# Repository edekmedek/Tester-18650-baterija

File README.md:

# Tester18650 R26 — dovršeno trasiranje i DRC

Izvorni R25 projekt u `Downloads` nije mijenjan. R26 je zasebna radna kopija.

## Napravljene promjene

- D1 i R5 premješteni su s koordinata izvan ploče na pločicu.
- R1, R2, R3 i R4 preraspoređeni su tako da nema fizičkih preklapanja s NodeMCU, INA219 i držačem baterije.
- Sve definirane mreže trasirane su na F.Cu i B.Cu.
- Vodovi snage (`BAT_PLUS`, `BAT_MINUS_GND`, `LOAD_PLUS`, `LOAD_RETURN`) izvedeni su širinom 1,0 mm.
- Upravljački i mjerni vodovi izvedeni su širinama 0,5–0,6 mm.
- Rub silkscreena INA219 footprinta povučen je unutar obrisa ploče.
- Sakriveni su natpisi koji su prelazili preko padova ili ruba ploče.

## Završni DRC

- DRC violations: 7 upozorenja, 0 grešaka
- Unconnected pads: 0
- Footprint errors: 0
- Nema kratkih spojeva, clearance grešaka, presijecanja vodova ni courtyard preklapanja.

Svih 7 preostalih upozorenja su `lib_footprint_mismatch`: lokalno prilagođeni footprintovi u PCB-u razlikuju se od primjeraka u projektnoj biblioteci. Nisu automatski zamijenjeni jer bi osvježavanje iz biblioteke moglo vratiti ranija, nepotvrđena mapiranja pinova.

## Obavezna provjera prije izrade

- Potvrditi fizičku orijentaciju zaštitne diode D1.
- Potvrditi INA219 IN+/IN− orijentaciju na stvarnom modulu.
- Iako je Q1 mapiranje ranije označeno kao korisnički potvrđeno, preporučuje se završna usporedba s točnom izvedbom C3209 prije narudžbe PCB-a.
- Provjeriti termički razmak i očekivanu disipaciju oba otpornika 22 Ω / 5 W u stvarnom kućištu.

Datoteka `DRC_R26.txt` sadrži puni završni izvještaj.

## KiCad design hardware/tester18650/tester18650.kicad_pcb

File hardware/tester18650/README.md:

# Tester 18650 — KiCad 10, shema R2 i PCB P3

**Funkcionalni strujni krug je spojen u uređivoj shemi. Fizičko ožičenje i C3209 pinout nisu potvrđeni. ERC nije čist: 11 pogrešaka i 1 upozorenje.**

R2 nastavlja postojeći projekt iz commita `bfc8b56`: isti `.kicad_pro`, isti list i isti UUID-i jedanaest zadržanih simbola. Nije izrađen zaseban projekt. Prekidi TP1–TP4 uklonjeni su i zamijenjeni stvarnim električnim vodovima. Raspored lista i oznake priključaka uređeni su radi čitljivosti.

## PCB prema fotografijama

Dodan je [uređivi PCB P3](tester18650.kicad_pcb), [PDF komponenti](tester18650_pcb_components.pdf), [PDF prednjeg bakra](tester18650_pcb_layout.pdf) i [3D prikaz](tester18650_pcb_3d.png). Raspored koristi korisnikove fotografije kao glavni vizualni izvor. Detalji, izvori footprintova i ograničenja su u [PCB.md](PCB.md). P3 ima osam mapiranih K1 padova te rutirane COM/BAT+ i NO/opterećenje; ukupno 33 segmenta na sedam bakrenih mreža. Q1 pinout ostaje nepotvrđen. Referentni/zamjenski 3D modeli jasno su označeni. **DRC: 2 nepovezane veze + 5 upozorenja usporedbe sa shemom; nije za proizvodnju.**

## Funkcionalni krug u shemi

```text
BAT+ → K1 COM (11) → NO (14) → (R1 22 Ω / 5 W || R2 22 Ω / 5 W)
     → VIN+ → RSH1, interni shunt INA219 → VIN− → BAT−
```

COM–NO koristi se prema korisnikovu zadatku i ponašanju firmwarea: aktivacija releja uključuje opterećenje. NC (12) ne sudjeluje u pražnjenju; ostavljen je otvoren i njegov je ERC nalaz vidljiv. Pet funkcija 11/12/14 i A1/A2 sada je mapirano na osam padova K1 prema korisnikovoj proizvođačkoj potvrdi i provjerljivoj KiCad 16A referenci. Izravna usporedba točnih TE dimenzija/tolerancija ostaje otvorena; mapiranje ne potvrđuje fizičko ožičenje korisnikova primjerka.

**VIN+ je spojen prema opterećenju, VIN− prema BAT− kao izričito označena projektna pretpostavka.** Firmware koristi `fabsf(ina219_current)`, pa pozitivna prikazana struja nije dokaz fizičkog polariteta. RSH1 prikazuje postojeći interni mjerni element modula, ne dodatni vanjski otpornik. Njegova je vrijednost označena `vrijednost ?`; firmware parametar `0.11425 Ω` naveden je zasebno kao kalibracijski podatak. RSH1 je izuzet iz zasebnog BOM-a i PCB-a jer pripada modulu.

Zavojnica K1 ostaje spojena između +5 V i kolektora Q1, oznake C3209. Nazivna zavojnica je 6 V DC, a dokumentirani pogon 5 V. Nije provjerena margina uklapanja. Q1 koristi generički NPN simbol; B/C/E su funkcije, a 1/2/3 nisu potvrđeni raspored nožica kućišta.

## Izvori za upravljanje i mjerenje

Pregledan je puni [ESPHome firmware](../../firmware/battery-tester-8266-wifi-test.yaml), njegov [opis](../../firmware/README.md), aktualna dokumentacija i korisnikove potvrde. Stare D6–D12 sheme nisu korištene kao dokaz.

Firmware potvrđuje `nodemcuv2`, GPIO14 bez inverzije (`ALWAYS_OFF` i isključenje pri bootu), SDA GPIO2, SCL GPIO5, I²C 100 kHz, INA219 `0x40` i A0 s faktorom `9.5079`. Prikazane su i radne napomene: uključivanje nakon 500 ms i početni cutoff 3,00 V kroz pet uzastopnih sekundi. Firmware nije izmijenjen ni flashan.

Firmware ne određuje bazni otpornik, spoj emitera, zaštitnu diodu, redoslijed otpornika djelitelja ni napajanja modula. Zato nema izmišljenog otpornika između GPIO14 i baze, izravnog kratkog spoja GPIO14–B, pretpostavljenog emitera na masi ni odabranog redoslijeda R3/R4. Pouzdani spojevi +5 V → zavojnica → kolektor i GPIO-i su nacrtani; preostale granice jasno su označene N3/N4. R3 = 10 kΩ i R4 = 20 kΩ zadržani su s otvorenim krajevima jer faktor A0 ne određuje njihovu fizičku topologiju.

## Logička sučelja i oznake

J1/J2 koriste standardni `Connector_Generic:Conn_01x06` kao logičke prikaze modula. Od faze P1 povezani su s referentnim PCB footprintovima i uključeni u pločicu/BOM; to nije potvrda mehaničkog pristajanja konkretnih modula. **Brojevi 1–6 su indeksi sheme, ne fizički raspored nožica.** Svaki priključak dodatno je označen funkcijom na listu. TP5 i TP6 su samo dokumentacijski završeci prema nepoznatom baznom sklopu i djelitelju; nisu ugrađene testne točke.

| Indeks | J1 — NodeMCU ESP8266 | J2 — INA219 modul |
|---|---|---|
| 1 | D5 / GPIO14 → TP5, bazni sklop nepoznat | SDA ↔ GPIO2 |
| 2 | D4 / GPIO2 ↔ SDA | SCL ↔ GPIO5 |
| 3 | D1 / GPIO5 ↔ SCL | VCC, otvoreno |
| 4 | A0 / ADC0 → TP6, djelitelj nepoznat | GND, otvoreno |
| 5 | Napajanje pločice, otvoreno | VIN+ ↔ opterećenje i RSH1/1 |
| 6 | GND ↔ BAT− prema dokumentu D2 | VIN− ↔ RSH1/2 i BAT−, projektna pretpostavka |

`BAT_MINUS` je jedini naziv povratne mreže, uključujući funkcionalni VIN−. `VIN_PLUS` je mreža između opterećenja i ulaza internog shunta. GND modula INA219 nije automatski spojen na VIN−/BAT−.

## Preostale nepoznanice

| Oznaka | Stanje u R2 |
|---|---|
| N1 | COM–NO funkcionalno spojen; K1 je mapiran na 8 padova 16A KiCad reference. Točne TE dimenzije/tolerancije nisu izravno očitane; ožičenje stvarnog primjerka nije potvrđeno. NC je nekorišten. |
| N2 | VIN+/VIN− i interni shunt spojeni u serijski put. Orijentacija je pretpostavka; fizički polaritet, vrijednost i izvedba shunta nisu izmjereni. |
| N3 | Baza i emiter C3209, fizički pinout, bazni otpornik i zaštitna dioda nisu potvrđeni. Otvoreni B/E i prekid nakon TP5 ostaju vidljivi. |
| N4 | Vrijednosti 10 kΩ/20 kΩ su poznate; njihovi krajevi, redoslijed i eventualni djelitelj na NodeMCU-u nisu. TP6 i R3/R4 ostaju bez pretpostavljenih veza. |
| N5 | GND INA219 te vrijednosti i naponska domena I²C pull-upova nisu potvrđeni. J2 GND je otvoren. |
| N6 | Izvor +5 V za relej, ulaz napajanja NodeMCU-a i VCC INA219 nisu utvrđeni. J1/5 i J2/3 su otvoreni. |

OLED nije ugrađen i nije nacrtan. Nisu dodani nepotvrđeni zaštitni elementi. PCB P3 koristi potvrđeni raster samo korisnikova izreza, uz mapirani osmoizvodni K1 i nedodijeljene Q1 padove i nepotvrđena kućišta; nema proizvoljne rekonstrukcije električnih mreža. Shema i PCB nisu odobrenje za proizvodnju ni potvrda sigurnosti fizičkog uređaja.

## Datoteke i provjera

- [KiCad projekt](tester18650.kicad_pro) i [uređiva shema](tester18650.kicad_sch).
- [Završni PDF](tester18650.pdf), A3 vodoravno, izvezen KiCadom 10.0.4 i vizualno pregledan.
- [ERC tumačenje](reports/ERC.md), [izvorni tekst](reports/erc.rpt) i [JSON](reports/erc.json).
- [Izvezene mreže](reports/netlist.xml), [rezultat provjere spojeva](reports/connectivity-check.txt), [provedena validacija](reports/VALIDATION.md).

```sh
cd /workspace/Tester-18650-baterija/hardware/tester18650
./tools/validate.sh
```

Skripta ponovno izvozi PDF i netlist, pokreće nativni ERC s `--exit-code-violations`, provjerava točne mreže i oba stanja radnog kontakta te zapisuje kontrolne zbrojeve. **Vraća status 5 jer ERC nije čist**, čak i kada provjera funkcionalnog puta prolazi. Ne mijenja se ozbiljnost ERC nalaza i ne dodaju se izuzeća, `No Connect` ili `PWR_FLAG` oznake. NC nalaz također je zadržan.

`tools/check_connectivity.py` može se pokrenuti zasebno: provjerava upravo izvezene mreže, zatvoren/otvoren COM–NO, obje paralelne grane i odsutnost premosnice opterećenja. To je provjera grafa spojeva, ne SPICE simulacija ili mjerenje struje. Kontrolni zbrojevi provjeravaju se naredbom `sha256sum -c reports/SHA256SUMS`.

KiCad 10 već je pripremljen u cloudu. `tools/kicad.sh` bira tu instalaciju ili `kicad-cli` na PATH-u; može se zadati `KICAD_CLI`. Standardne biblioteke koristi preko `KICAD10_SYMBOL_DIR`. Na istom Debian 13 amd64 računalu instalacija se po potrebi ponavlja s `./tools/install_cloud.sh`; ostale platforme trebaju službenu KiCad 10 instalaciju i Python 3.

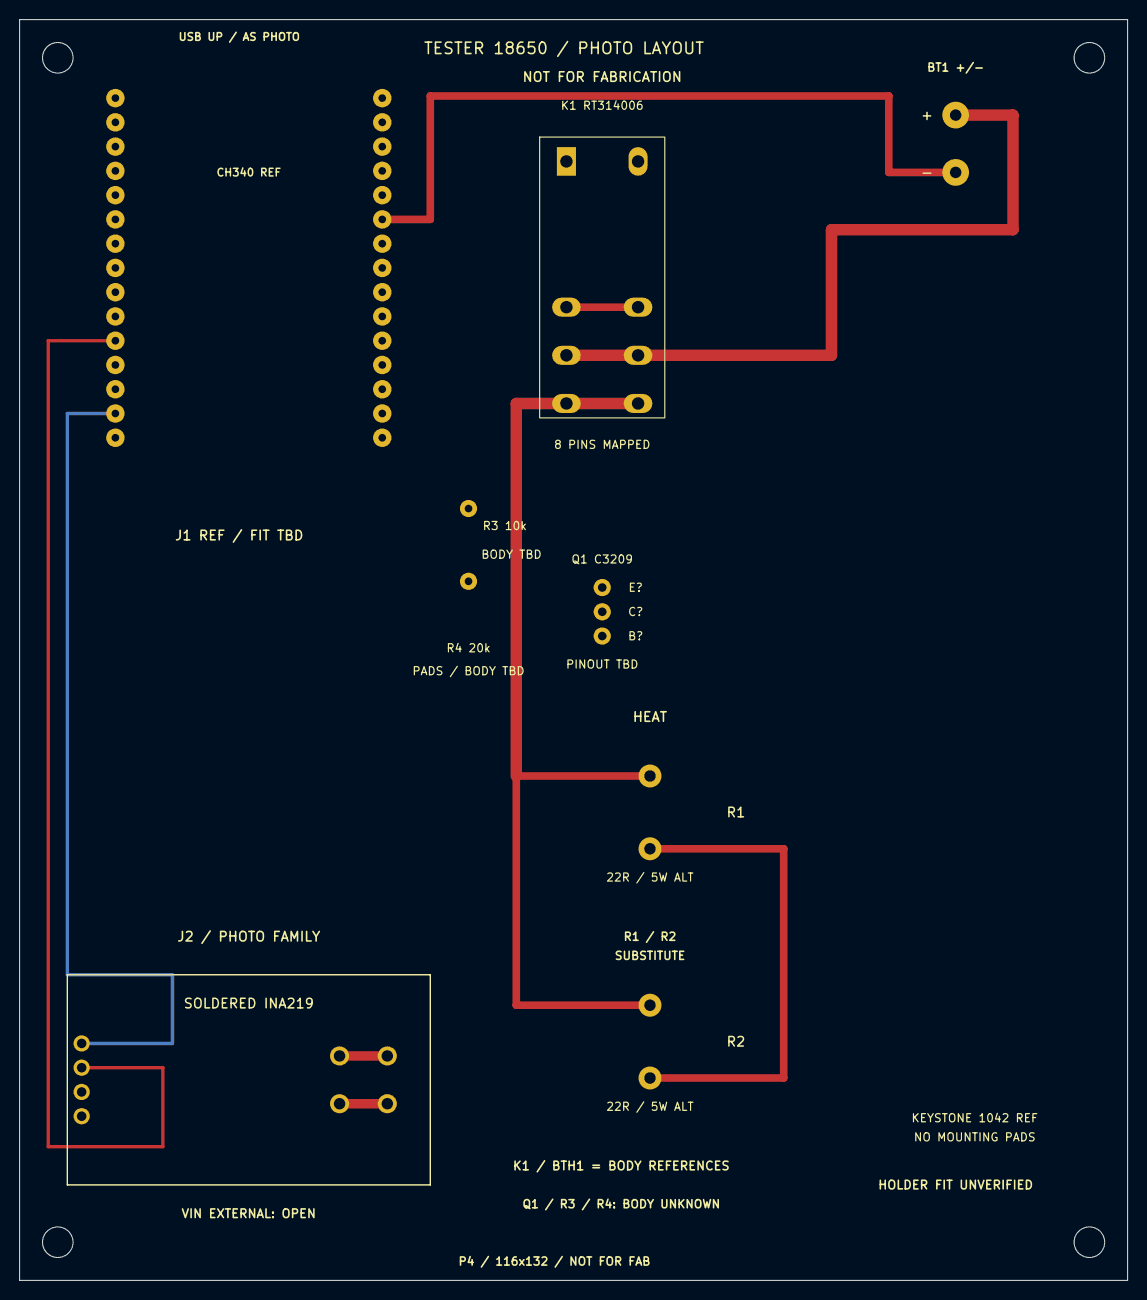
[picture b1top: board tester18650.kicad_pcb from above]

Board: 2 copper layers, 116.0 x 132.0 mm, 14 parts (0 on the bottom side), 6 nets.

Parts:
BT1: Li-ion 18650; Battery_Wire_Termination_DESIGN
BTH1: 18650 holder allocation only; Keystone1042_LAYOUT_REFERENCE_NO_PADS
H1, H2, H3, H4: M3 / DESIGN; MountingHole_3.2mm_M3
J1: NodeMCU v2; NodeMCU_CH340_Manufacturer_REFERENCE
J2: INA219 / 0x40; INA219_Soldered333066_Manufacturer_REF
K1: Schrack RT314006; RT314006_16A_8PIN_5MM_KICAD_REFERENCE
Q1: C3209 / NPN; C3209_CROP_GRID_UNMAPPED
R1, R2: 22 Ω / 5 W; Cement_5WAXIAL_VERTICAL_7.62_SUBSTITUTE
R3: 10 kΩ; R3_CROP_GRID_7.62_BODY_TBD
R4: 20 kΩ; R4_LABEL_ONLY_NO_PADS

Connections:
/BAT_MINUS: BT1.2, J1.6, J2.6
/BAT_PLUS: BT1.1, K1.11
/I2C_SCL_GPIO5: J1.3, J2.2
/I2C_SDA_GPIO2: J1.2, J2.1
/LOAD_IN: K1.14, R1.1, R2.1
/VIN_PLUS: J2.5, R1.2, R2.2

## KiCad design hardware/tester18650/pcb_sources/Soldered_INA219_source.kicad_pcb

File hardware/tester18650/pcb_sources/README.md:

# Izvori geometrije i podrijetlo

Primarni vizualni izvor je korisnikov `tester18650_fotoreferenca_obje_strane.pdf` (jedna stranica, gornja strana lijevo, donja strana već zrcaljena desno). Datoteka nema potvrđeno mjerilo za PCB; korišten je raspored, ne izmišljene milimetarske mjere. SHA-256 i naziv zabilježeni su u [manifestu](reference-geometry.json). Korisnikove fotografije nisu kopirane u javni repozitorij.

## NodeMCU CH340 referenca

Proizvođački otvoreni projekt: [nodemcu/nodemcu-devkit](https://github.com/nodemcu/nodemcu-devkit), commit `b0f19d6d1c49b6db4aef56ddba789a7f92f6ecce`, `ESP12_DEVKIT.lbr`. Kopija je [NodeMCU_CH340_reference.lbr](NodeMCU_CH340_reference.lbr), licenca [MIT](NODEMCU_LICENSE.txt). Footprint P1 izveden je iz tih koordinata i okrenut s USB-om prema gore. Ne tvrdi se da je proizvođački povijesni DevKit isti kao fotografirani klon Ver 0.1; konkretna geometrija klona ostaje blokator.

## Soldered INA219

Proizvođački projekt: [Voltage---current-sensor-INA219-breakout-hardware-design](https://github.com/SolderedElectronics/Voltage---current-sensor-INA219-breakout-hardware-design), commit `bcd0be51f51a1b68144ee6343d713c3ba74b0f48`.

- Original `CAD/V1.0.0/INA219_breakout.kicad_pcb` spremljen je nepromijenjen kao [Soldered_INA219_source.kicad_pcb](Soldered_INA219_source.kicad_pcb).
- Originalni proizvođački `OUTPUTS/V1.0.0/Voltage & current sensor INA219 breakout 3D.step` je [Soldered_INA219_source.step](Soldered_INA219_source.step).
- Geometrijski izvadak s koordinatama izvoda i izvornim SHA-256 je u manifestu. Izravno su provjereni obris 38 × 22 mm i funkcije četiriju upravljačkih kontakata.
- Za fotografiranu varijantu uklonjeno je **samo jedno opcijsko tijelo vijčanog terminala**, jer se na slici jasno vide prazni strujni otvori. Preostalih 28 proizvođačkih tijela sačuvano je bez novih dimenzija. Rezultat je `models/Soldered_INA219_photo_variant.step`, reprodukcija u `tools/adapt_ina_model.py`, zapis u `reports/pcb/ina-model-adaptation.json`.
- Priložena je [proizvođačka TAPR OHL licenca](SOLDERED_LICENSE.md). Izvedeni footprint i prilagođeni model zadržavaju ovo podrijetlo i licencu. Ostala geometrija izvora nije predstavljena kao nova autorska geometrija.

## Područja bez potvrđenog paketa

R1/R2, R3/R4, Q1, K1 i BTH1 koriste jasno imenovane `RESERVE_*_PACKAGE_TBD` položaje bez padova. Njihove dimenzije su **dodijeljene površine na novoj pločici**, ne mjere stvarnog dijela. STEP plohe tih oznaka imaju grafičku debljinu 0,02 mm; to nisu modeli kućišta. Fotografije nisu korištene za izmišljanje dubine, visine ili razmaka nevidljivih izvoda.

Pregledane su standardne KiCad Schrack RT1 varijante, no nisu nasumično zamijenjene za RT314006. Povezani proizvođački PDF-ovi na Schrack/TE odredištima nisu bili dostupni iz ovog okruženja (HTTP proxy 403), a biblioteke sadrže različite rasporede/varijante. Zato taj korak nije označen kao verificiran.

## Alati i provjera

Generiranje početnih objekata koristilo je instalirani `pcbnew` Python API 9.0.2. Konačni PCB je zatim nativno spremljen/učitan u KiCadu **10.0.4**, format `20260206`; PDF, GLB i DRC izvozi izvedeni su KiCadom 10. Dimenzije nisu potvrđivane samo sintaktičkom provjerom teksta.

Grafičke CAD plohe i preinaka proizvođačkog modela koriste OpenCascade preko `cadquery-ocp==7.8.1.1.post1`. To nije potrebno za otvaranje predanog PCB-a ili njegovih već priloženih STEP modela. PNG je render iz stvarnog KiCad GLB-a u Blenderu 4.3.2, uz dodatne grafičke oznake referenci na rezerviranim plohama. Izvorni KiCad CLI renderer u ovom je okruženju završavao statusom 139; nije prikazano da je taj poziv prošao.

Za sve primijenjene izvore uključen je izvorni CAD ili točan javni URL/commit. Nisu objavljeni Wi-Fi podaci, tajne niti drugi firmware parametri izvan već javnog repozitorija.

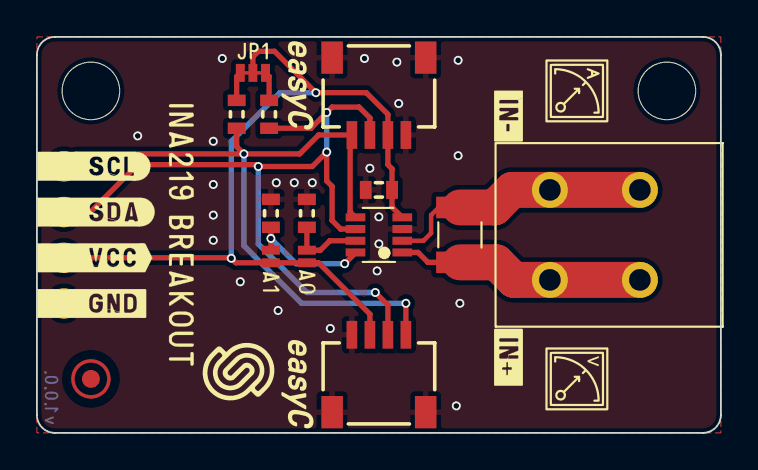
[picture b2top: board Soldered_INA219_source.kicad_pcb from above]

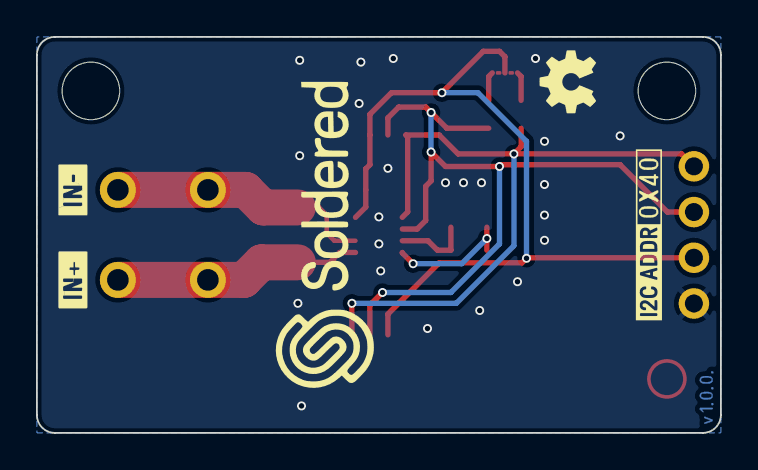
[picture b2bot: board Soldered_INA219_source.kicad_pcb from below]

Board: 2 copper layers, 38.0 x 22.0 mm, 18 parts (2 on the bottom side), 10 nets.

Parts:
C1: 100nF; 0603C
FD1: FIDUCIAL; FIDUCIAL_23
H1, H2: HOLE_3.2mm
JP1: SMD_JUMPER_3_PAD_TRACE
JP2, JP3: SMD_JUMPER
K1: TERMINAL_KF235-5.0-2P
K2, K4: easyC-SMD; easyC-connector
K3: HEADER_MALE_4X1
R1, R2, R3, R4: 10k; 0603R
R5: 0R1; 1210R
Ref**: Val**; Version1.0.0.
U1: INA219; SOT23-8

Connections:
A0: JP2.1, R3.2, U1.7 (A0)
A1: JP3.1, R4.2, U1.8 (A1)
GND: C1.2, K2.4 (GND), K2.5 (SHIELD), K3.1, K4.4 (GND), K4.5 (SHIELD), R3.1, R4.1, U1.3 (GND)
IN+: K1.2, R5.2, U1.1 (IN+)
IN-: K1.1, R5.1, U1.2 (IN-)
unnamed: JP1.1, R2.2
unnamed: JP1.3, R1.1
SCL: K2.1 (SCL), K3.4, K4.1 (SCL), R2.1, U1.5 (SCL)
SDA: K2.2 (SDA), K3.3, K4.2 (SDA), R1.2, U1.6 (SDA)
VCC: C1.1, JP1.2, JP2.2, JP3.2, K2.3 (3V3), K3.2, K4.3 (3V3), U1.4 (VS)
